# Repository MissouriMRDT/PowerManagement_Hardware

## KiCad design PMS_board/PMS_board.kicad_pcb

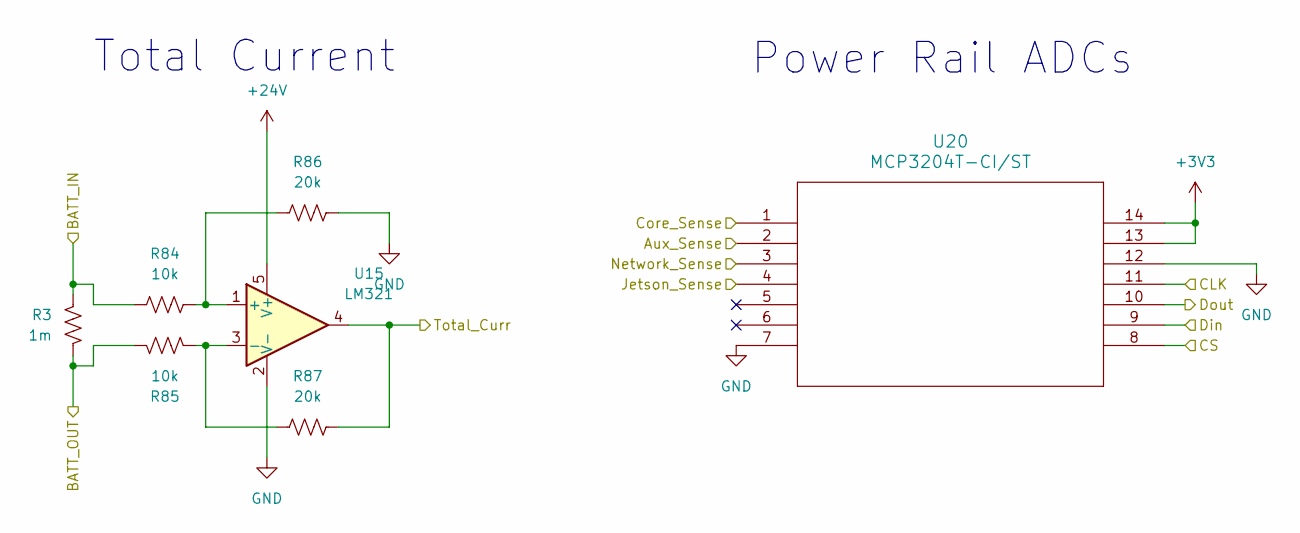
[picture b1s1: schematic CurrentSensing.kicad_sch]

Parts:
R3: 1m; ShuntSMD_BVT-M-R001-1.0
R84, R85: 10k; R_0603_1608Metric_Pad0.98x0.95mm_HandSolder
R86, R87: 20k; R_0603_1608Metric_Pad0.98x0.95mm_HandSolder
U15: LM321; SOT-23-5
U20: MCP3204T-CI/ST; TSSOP14_MC_MCH

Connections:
+3V3: U20.13, U20.14; also elsewhere on the board
+24V: U15.5 (V+); also elsewhere on the board
/Current Sensing/Aux_Sense: U20.2; also elsewhere on the board
/Current Sensing/BATT_OUT: R3.2, R85.1; also elsewhere on the board
/Current Sensing/CLK: U20.11; also elsewhere on the board
/Current Sensing/CS: U20.8; also elsewhere on the board
/Current Sensing/Core_Sense: U20.1; also elsewhere on the board
/Current Sensing/Din: U20.9; also elsewhere on the board
/Current Sensing/Dout: U20.10; also elsewhere on the board
/Current Sensing/Jetson_Sense: U20.4; also elsewhere on the board
/Current Sensing/Network_Sense: U20.3; also elsewhere on the board
/Current Sensing/Total_Curr: R87.2, U15.4; also elsewhere on the board
/HotSwap/Aalmout: R3.1, R84.1; also elsewhere on the board
GND: R86.2, U15.2 (V-), U20.7, U20.12; also elsewhere on the board
unnamed: R84.2, R86.1, U15.1 (+)
unnamed: R85.2, R87.1, U15.3 (-)

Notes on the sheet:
Total Current
Power Rail ADCs

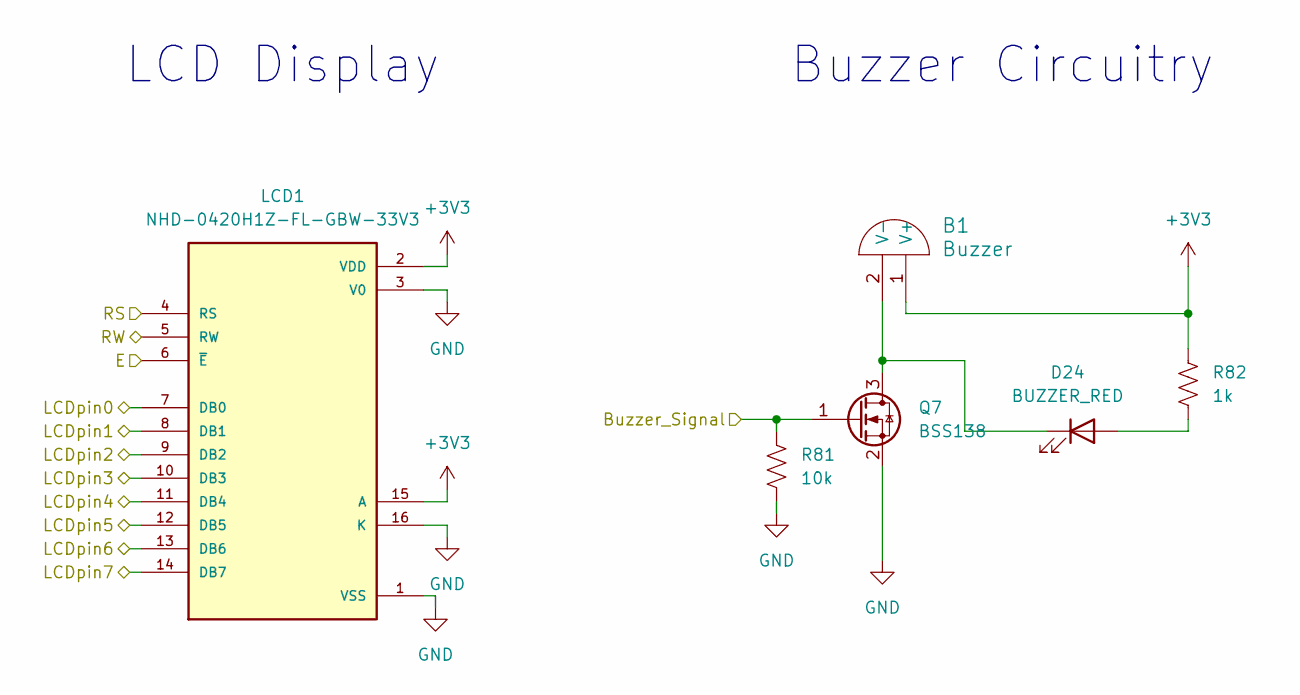
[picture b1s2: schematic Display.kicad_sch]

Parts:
B1: Buzzer; Buzzer_12x9.5RM7.6
D24: BUZZER_RED; LED_0603_1608Metric_Pad1.05x0.95mm_HandSolder
LCD1: NHD-0420H1Z-FL-GBW-33V3; LCD_NHD-0420H1Z-FL-GBW-33V3; PARTREV 02
Q7: BSS138; SOT-23
R81: 10k; R_0603_1608Metric_Pad0.98x0.95mm_HandSolder
R82: 1k; R_0603_1608Metric_Pad0.98x0.95mm_HandSolder

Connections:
+3V3: B1.1 (V+), LCD1.2 (VDD), LCD1.15 (A), R82.1; also elsewhere on the board
/Battery Display/Buzzer_Signal: Q7.1 (G), R81.1; also elsewhere on the board
/Battery Display/E: LCD1.6 (~E); also elsewhere on the board
/Battery Display/LCDpin0: LCD1.7 (DB0); also elsewhere on the board
/Battery Display/LCDpin1: LCD1.8 (DB1); also elsewhere on the board
/Battery Display/LCDpin2: LCD1.9 (DB2); also elsewhere on the board
/Battery Display/LCDpin3: LCD1.10 (DB3); also elsewhere on the board
/Battery Display/LCDpin4: LCD1.11 (DB4); also elsewhere on the board
/Battery Display/LCDpin5: LCD1.12 (DB5); also elsewhere on the board
/Battery Display/LCDpin6: LCD1.13 (DB6); also elsewhere on the board
/Battery Display/LCDpin7: LCD1.14 (DB7); also elsewhere on the board
/Battery Display/RS: LCD1.4 (RS); also elsewhere on the board
/Battery Display/RW: LCD1.5 (RW); also elsewhere on the board
GND: LCD1.1 (VSS), LCD1.3 (V0), LCD1.16 (K), Q7.2 (S), R81.2; also elsewhere on the board
unnamed: B1.2 (V-), D24.1 (K), Q7.3 (D)
unnamed: D24.2 (A), R82.2

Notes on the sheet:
Buzzer Circuitry
LCD Display

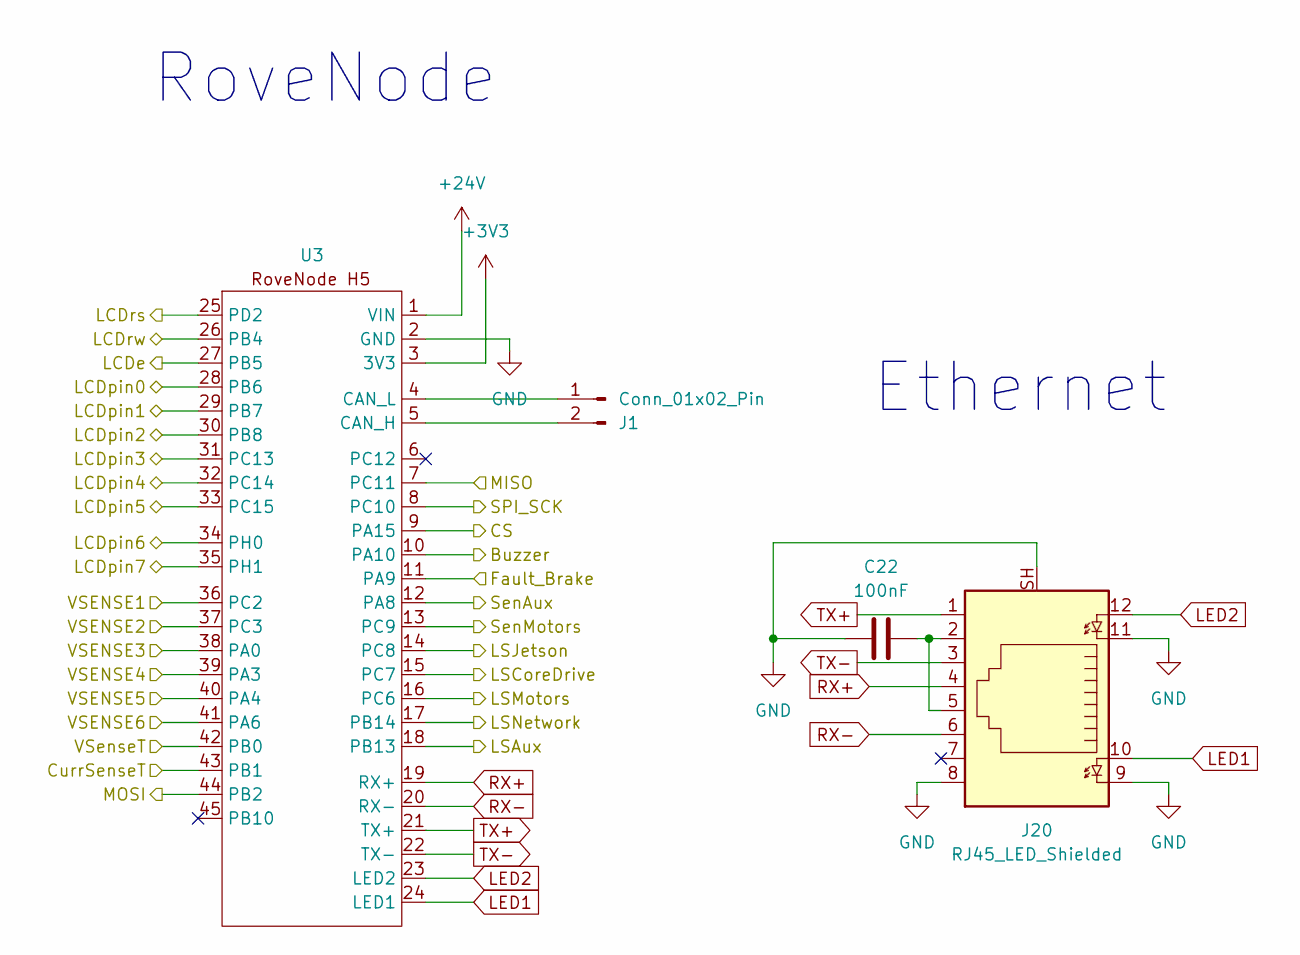
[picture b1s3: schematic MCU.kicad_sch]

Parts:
C22: 100nF; C_0603_1608Metric_Pad1.08x0.95mm_HandSolder
J1: Conn_01x02_Pin; JST_PH_B2B-PH-K_1x02_P2.00mm_Vertical
J20: RJ45_LED_Shielded; RJ45_Teensy
U3: RoveNode_H5

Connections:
+3V3: U3.3 (3V3); also elsewhere on the board
+24V: U3.1 (VIN); also elsewhere on the board
/Battery Display/Buzzer_Signal: U3.10 (PA10); also elsewhere on the board
/Battery Display/E: U3.27 (PB5); also elsewhere on the board
/Battery Display/LCDpin0: U3.28 (PB6); also elsewhere on the board
/Battery Display/LCDpin1: U3.29 (PB7); also elsewhere on the board
/Battery Display/LCDpin2: U3.30 (PB8); also elsewhere on the board
/Battery Display/LCDpin3: U3.31 (PC13); also elsewhere on the board
/Battery Display/LCDpin4: U3.32 (PC14); also elsewhere on the board
/Battery Display/LCDpin5: U3.33 (PC15); also elsewhere on the board
/Battery Display/LCDpin6: U3.34 (PH0); also elsewhere on the board
/Battery Display/LCDpin7: U3.35 (PH1); also elsewhere on the board
/Battery Display/RS: U3.25 (PD2); also elsewhere on the board
/Battery Display/RW: U3.26 (PB4); also elsewhere on the board
/Current Sensing/CLK: U3.8 (PC10); also elsewhere on the board
/Current Sensing/CS: U3.9 (PA15); also elsewhere on the board
/Current Sensing/Din: U3.44 (PB2); also elsewhere on the board
/Current Sensing/Dout: U3.7 (PC11); also elsewhere on the board
/Current Sensing/Total_Curr: U3.43 (PB1); also elsewhere on the board
/Load Switching + Outputs/Fault_Brakes: U3.11 (PA9); also elsewhere on the board
/Load Switching + Outputs/In_Aux: U3.18 (PB13); also elsewhere on the board
/Load Switching + Outputs/In_Boards: U3.15 (PC7); also elsewhere on the board
/Load Switching + Outputs/In_Jetson: U3.14 (PC8); also elsewhere on the board
/Load Switching + Outputs/In_Motors: U3.16 (PC6); also elsewhere on the board
/Load Switching + Outputs/In_Network: U3.17 (PB14); also elsewhere on the board
/Load Switching + Outputs/Sen_Aux: U3.12 (PA8); also elsewhere on the board
/Load Switching + Outputs/Sen_Motors: U3.13 (PC9); also elsewhere on the board
/Microcontroller/VSENSE1: U3.36 (PC2); also elsewhere on the board
/Microcontroller/VSENSE2: U3.37 (PC3); also elsewhere on the board
/Microcontroller/VSENSE3: U3.38 (PA0); also elsewhere on the board
/Microcontroller/VSENSE4: U3.39 (PA3); also elsewhere on the board
/Microcontroller/VSENSE5: U3.40 (PA4); also elsewhere on the board
/Microcontroller/VSENSE6: U3.41 (PA6); also elsewhere on the board
/Microcontroller/VSenseT: U3.42 (PB0); also elsewhere on the board
GND: C22.1, J20.8, J20.9, J20.11, J20.SH, U3.2 (GND); also elsewhere on the board
LED1: J20.10, U3.24 (LED1)
LED2: J20.12, U3.23 (LED2)
unnamed: C22.2, J20.2, J20.5
unnamed: J1.1, U3.4 (CAN_L)
unnamed: J1.2, U3.5 (CAN_H)
RX+: J20.4, U3.19 (RX+)
RX-: J20.6, U3.20 (RX-)
TX+: J20.1, U3.21 (TX+)
TX-: J20.3, U3.22 (TX-)

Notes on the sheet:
Ethernet
RoveNode

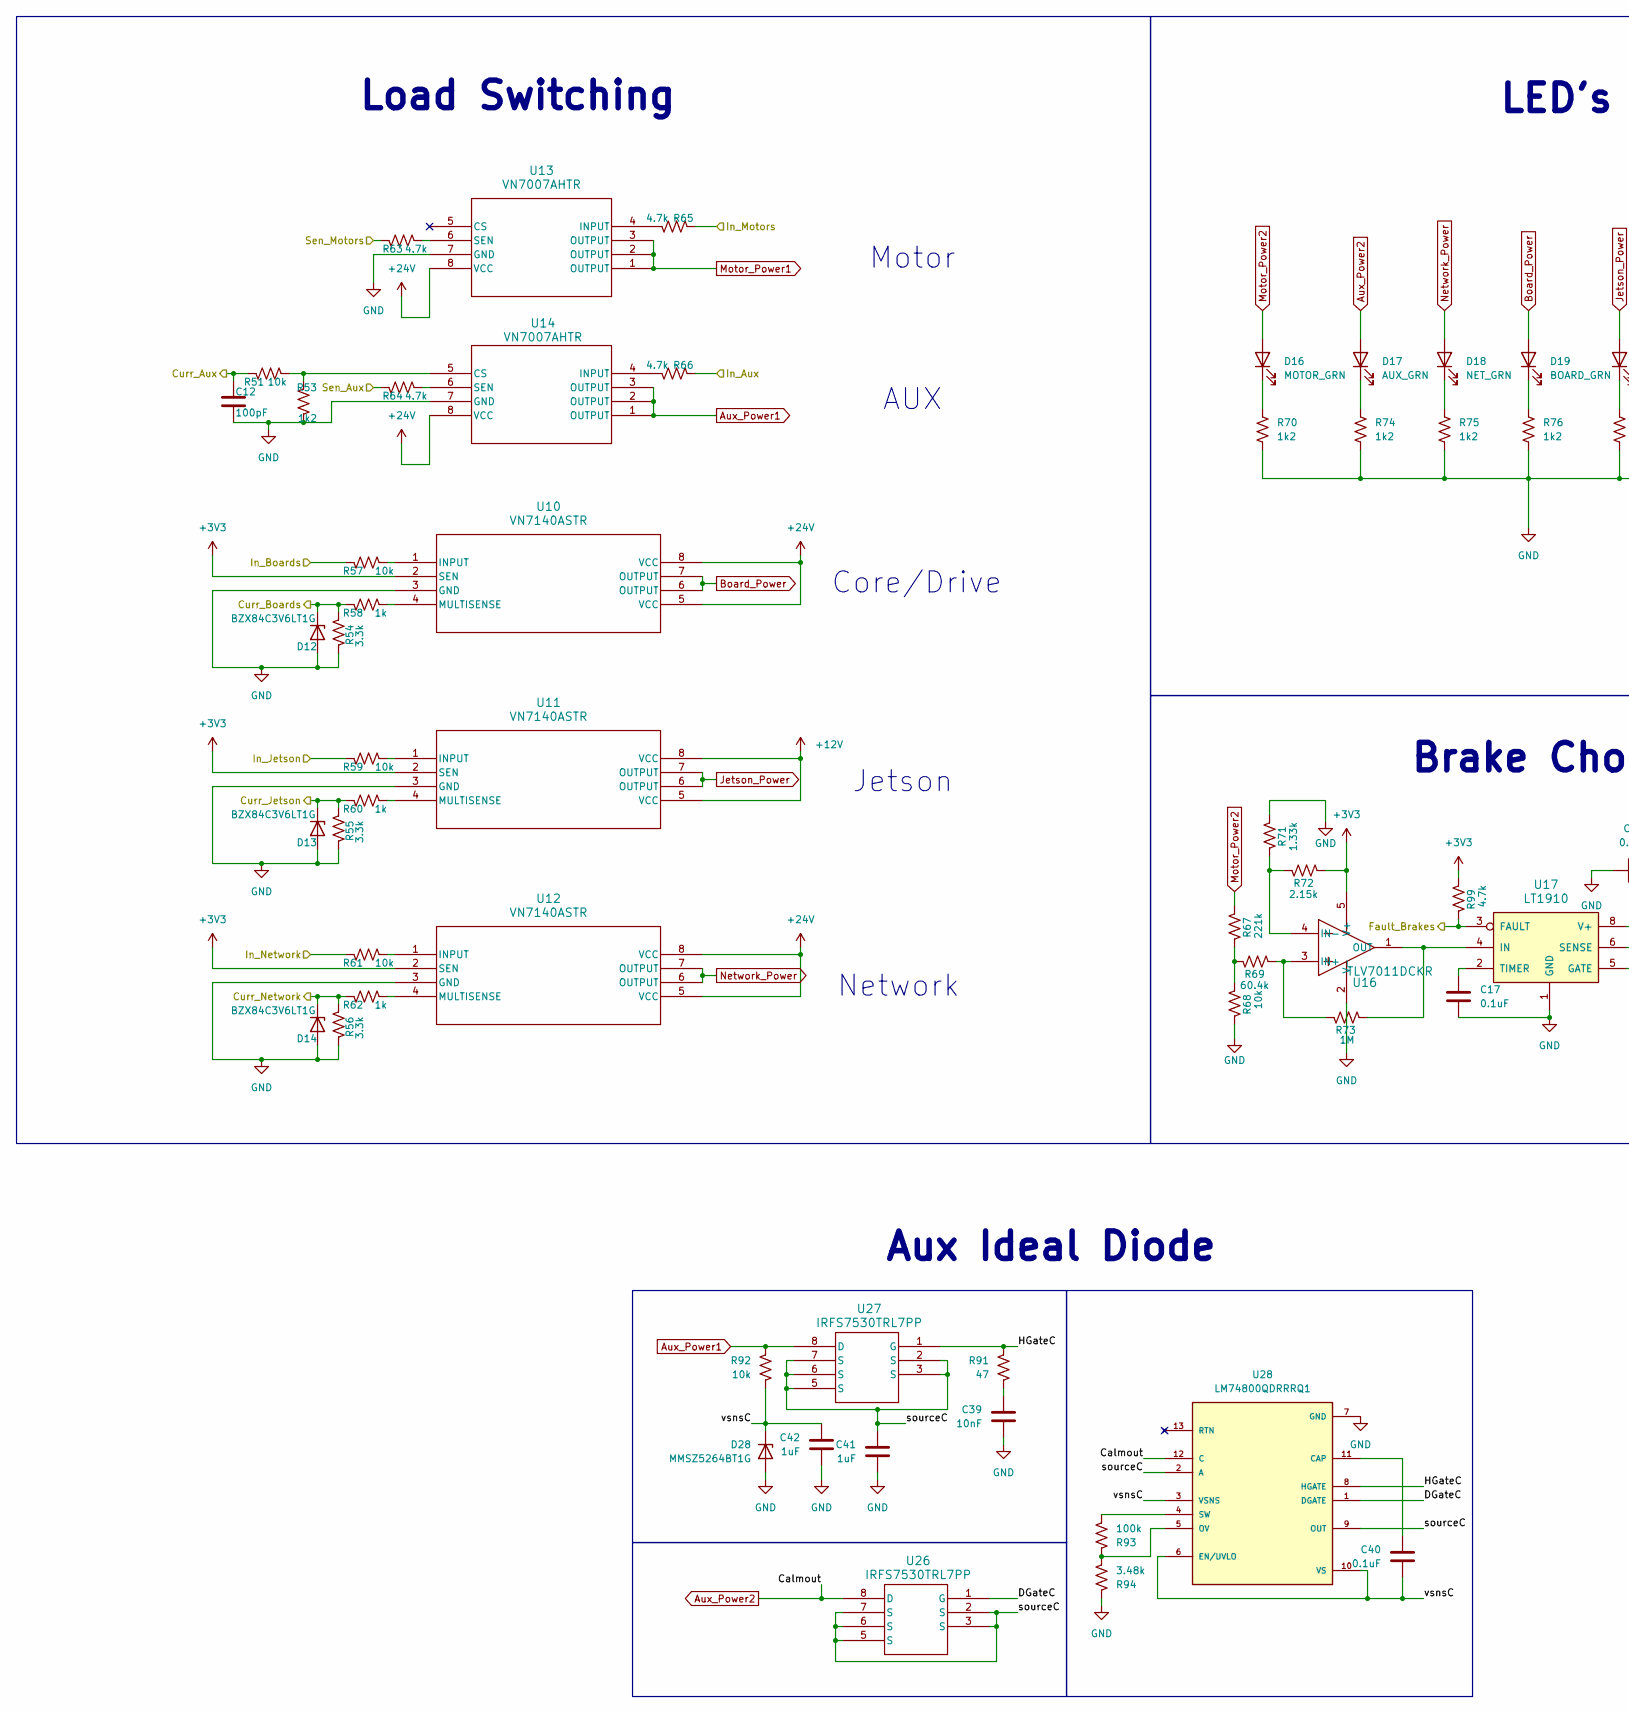
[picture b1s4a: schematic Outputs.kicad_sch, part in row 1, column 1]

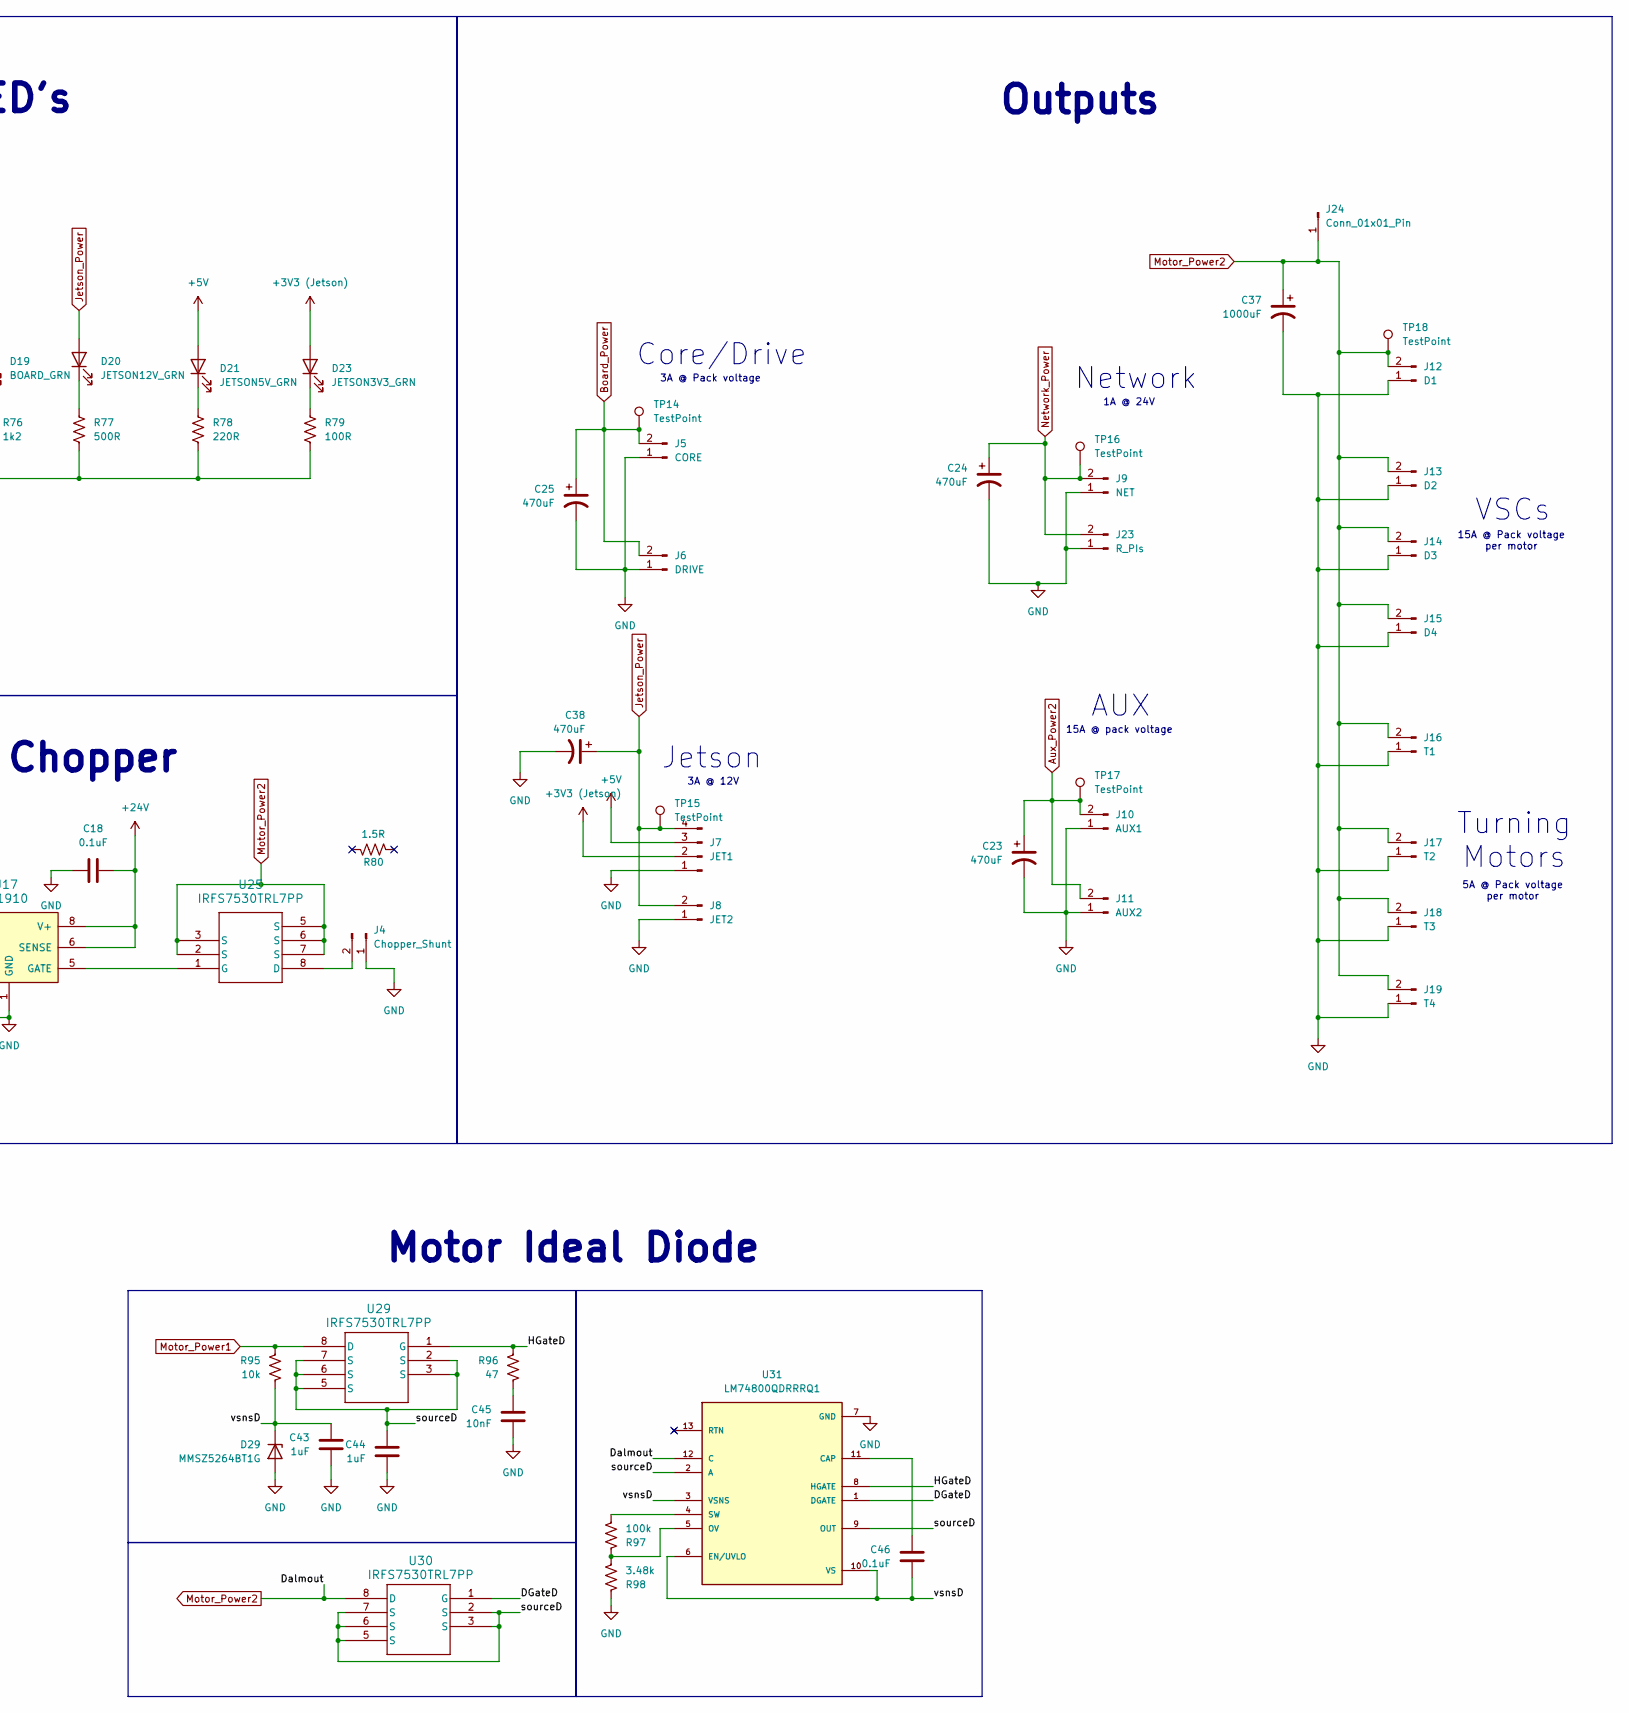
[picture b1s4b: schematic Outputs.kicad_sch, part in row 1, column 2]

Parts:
C12: 100pF; C_0603_1608Metric_Pad1.08x0.95mm_HandSolder
C17, C18, C40, C46: 0.1uF; C_0603_1608Metric_Pad1.08x0.95mm_HandSolder
C23, C24, C25, C38: 470uF; CP_Radial_D10.0mm_P5.00mm
C37: 1000uF; CP_Radial_D16.0mm_P7.50mm
C39, C45: 10nF; C_0603_1608Metric_Pad1.08x0.95mm_HandSolder
C41, C42, C43, C44: 1uF; C_0603_1608Metric_Pad1.08x0.95mm_HandSolder
D12, D13, D14: BZX84C3V6LT1G; SOT-23_Diode
D16: MOTOR_GRN; D_0603_1608Metric_Pad1.05x0.95mm_HandSolder
D17: AUX_GRN; D_0603_1608Metric_Pad1.05x0.95mm_HandSolder
D18: NET_GRN; D_0603_1608Metric_Pad1.05x0.95mm_HandSolder
D19: BOARD_GRN; D_0603_1608Metric_Pad1.05x0.95mm_HandSolder
D20: JETSON12V_GRN; D_0603_1608Metric_Pad1.05x0.95mm_HandSolder
D21: JETSON5V_GRN; D_0603_1608Metric_Pad1.05x0.95mm_HandSolder
D23: JETSON3V3_GRN; D_0603_1608Metric_Pad1.05x0.95mm_HandSolder
D28, D29: MMSZ5264BT1G; D_SOD-123
J4: Chopper_Shunt; MOLEX_MegaFit_02_Vertical
J5: CORE; MOLEX_MegaFit_02_Vertical
J6: DRIVE; MOLEX_MegaFit_02_Vertical
J7: JET1; MOLEX_SL_04_Vertical
J8: JET2; MOLEX_MegaFit_02_Vertical
J9: NET; MOLEX_MegaFit_02_Vertical
J10: AUX1; MOLEX_MegaFit_02_Vertical
J11: AUX2; MOLEX_MegaFit_02_Vertical
J12: D1; MOLEX_MegaFit_02_Vertical
J13: D2; MOLEX_MegaFit_02_Vertical
J14: D3; MOLEX_MegaFit_02_Vertical
J15: D4; MOLEX_MegaFit_02_Vertical
J16: T1; MOLEX_MegaFit_02_Vertical
J17: T2; MOLEX_MegaFit_02_Vertical
J18: T3; MOLEX_MegaFit_02_Vertical
J19: T4; MOLEX_MegaFit_02_Vertical
J23: R_PIs; MOLEX_MegaFit_02_Vertical
J24: Conn_01x01_Pin; Square_Anderson_1_V
R51, R57, R59, R61, R68, R92, R95: 10k; R_0603_1608Metric_Pad0.98x0.95mm_HandSolder
R53, R70, R74, R75, R76: 1k2; R_0603_1608Metric_Pad0.98x0.95mm_HandSolder
R54, R55, R56: 3.3k; R_0603_1608Metric_Pad0.98x0.95mm_HandSolder
R58, R60, R62: 1k; R_0603_1608Metric_Pad0.98x0.95mm_HandSolder
R63, R64, R65, R66, R99: 4.7k; R_0603_1608Metric_Pad0.98x0.95mm_HandSolder
R67: 221k; R_0603_1608Metric_Pad0.98x0.95mm_HandSolder
R69: 60.4k; R_0603_1608Metric_Pad0.98x0.95mm_HandSolder
R71: 1.33k; R_0603_1608Metric_Pad0.98x0.95mm_HandSolder
R72: 2.15k; R_0603_1608Metric_Pad0.98x0.95mm_HandSolder
R73: 1M; R_0603_1608Metric_Pad0.98x0.95mm_HandSolder
R77: 500R; R_0603_1608Metric_Pad0.98x0.95mm_HandSolder
R78: 220R; R_0603_1608Metric_Pad0.98x0.95mm_HandSolder
R79: 100R; R_0603_1608Metric_Pad0.98x0.95mm_HandSolder
R80: 1.5R
R91, R96: 47; R_0603_1608Metric_Pad0.98x0.95mm_HandSolder
R93, R97: 100k; R_0603_1608Metric_Pad0.98x0.95mm_HandSolder
R94, R98: 3.48k; R_0603_1608Metric_Pad0.98x0.95mm_HandSolder
TP14, TP15, TP16, TP17, TP18: TestPoint; TestPoint_Pad_D1.0mm
U10, U11, U12: VN7140ASTR; SO-8_STM
U13, U14: VN7007AHTR; OCTOPAK_STM
U16: TLV7011DCKR; DCK0005A_N
U17: LT1910; SO-8_3.9x4.9mm_P1.27mm
U25, U26, U27, U29, U30: IRFS7530TRL7PP; PG-TO263-7_INF
U28, U31: LM74800QDRRRQ1; IC_LM74800QDRRRQ1; PARTREV C

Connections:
+3V3: R72.2, R99.2, U10.2 (SEN), U11.2 (SEN), U12.2 (SEN), U16.5 (V+); also elsewhere on the board
+3V3 (Jetson): D23.2 (A), J7.2; also elsewhere on the board
+5V: D21.2 (A), J7.3; also elsewhere on the board
+12V: U11.5 (VCC), U11.8 (VCC); also elsewhere on the board
+24V: C18.2, U10.5 (VCC), U10.8 (VCC), U12.5 (VCC), U12.8 (VCC), U13.8 (VCC), U14.8 (VCC), U17.6 (SENSE), U17.8 (V+); also elsewhere on the board
/Current Sensing/Aux_Sense: C12.2, R51.2; also elsewhere on the board
/Current Sensing/Core_Sense: D12.1 (K), R54.2, R58.1; also elsewhere on the board
/Current Sensing/Jetson_Sense: D13.1 (K), R55.2, R60.1; also elsewhere on the board
/Current Sensing/Network_Sense: D14.1 (K), R56.2, R62.1; also elsewhere on the board
/Load Switching + Outputs/DGateC: U26.1 (G), U28.1 (DGATE)
/Load Switching + Outputs/DGateD: U30.1 (G), U31.1 (DGATE)
/Load Switching + Outputs/Fault_Brakes: R99.1, U17.3 (FAULT); also elsewhere on the board
/Load Switching + Outputs/HGateC: R91.1, U27.1 (G), U28.8 (HGATE)
/Load Switching + Outputs/HGateD: R96.1, U29.1 (G), U31.8 (HGATE)
/Load Switching + Outputs/In_Aux: R66.2; also elsewhere on the board
/Load Switching + Outputs/In_Boards: R57.1; also elsewhere on the board
/Load Switching + Outputs/In_Jetson: R59.1; also elsewhere on the board
/Load Switching + Outputs/In_Motors: R65.2; also elsewhere on the board
/Load Switching + Outputs/In_Network: R61.1; also elsewhere on the board
/Load Switching + Outputs/Sen_Aux: R64.2; also elsewhere on the board
/Load Switching + Outputs/Sen_Motors: R63.2; also elsewhere on the board
/Load Switching + Outputs/sourceC: C41.1, U26.2 (S), U26.3 (S), U26.5 (S), U26.6 (S), U26.7 (S), U27.2 (S), U27.3 (S), U27.5 (S), U27.6 (S), U27.7 (S), U28.2 (A), U28.9 (OUT)
/Load Switching + Outputs/sourceD: C44.1, U29.2 (S), U29.3 (S), U29.5 (S), U29.6 (S), U29.7 (S), U30.2 (S), U30.3 (S), U30.5 (S), U30.6 (S), U30.7 (S), U31.2 (A), U31.9 (OUT)
/Load Switching + Outputs/vsnsC: C40.2, C42.1, D28.1 (K), R92.1, U28.3 (VSNS), U28.6 (EN/UVLO), U28.10 (VS)
/Load Switching + Outputs/vsnsD: C43.1, C46.2, D29.1 (K), R95.1, U31.3 (VSNS), U31.6 (EN/UVLO), U31.10 (VS)
Aux_Power1: R92.2, U14.1 (OUTPUT), U14.2 (OUTPUT), U14.3 (OUTPUT), U27.8 (D)
Aux_Power2: C23.1, D17.2 (A), J10.2, J11.2, TP17.1 (1_1), U26.8 (D), U28.12 (C)
Board_Power: C25.1, D19.2 (A), J5.2, J6.2, TP14.1 (1_1), U10.6 (OUTPUT), U10.7 (OUTPUT)
GND: C12.1, C17.2, C18.1, C23.2, C24.2, C25.2, C37.2, C38.2, C39.2, C41.2, C42.2, C43.2, C44.2, C45.2, D12.2 (A), D13.2 (A), D14.2 (A), D28.2 (A), D29.2 (A), J4.1, J5.1, J6.1, J7.1, J8.1, J9.1, J10.1, J11.1, J12.1, J13.1, J14.1, J15.1, J16.1, J17.1, J18.1, J19.1, J23.1, R53.2, R54.1, R55.1, R56.1, R68.1, R70.2, R71.2, R74.2, R75.2, R76.2, R77.2, R78.2, R79.2, R94.1, R98.1, U10.3 (GND), U11.3 (GND), U12.3 (GND), U13.7 (GND), U14.7 (GND), U16.2 (V-), U17.1 (GND), U28.7 (GND), U31.7 (GND); also elsewhere on the board
Jetson_Power: C38.1, D20.2 (A), J7.4, J8.2, TP15.1 (1_1), U11.6 (OUTPUT), U11.7 (OUTPUT)
Motor_Power1: R95.2, U13.1 (OUTPUT), U13.2 (OUTPUT), U13.3 (OUTPUT), U29.8 (D)
Motor_Power2: C37.1, D16.2 (A), J12.2, J13.2, J14.2, J15.2, J16.2, J17.2, J18.2, J19.2, J24.1 (Pin_1_1), R67.2, TP18.1 (1_1), U25.2 (S), U25.3 (S), U25.5 (S), U25.6 (S), U25.7 (S), U30.8 (D), U31.12 (C)
unnamed: C39.1, R91.2
unnamed: C45.1, R96.2
unnamed: D16.1 (K), R70.1
unnamed: D17.1 (K), R74.1
unnamed: D18.1 (K), R75.1
unnamed: D19.1 (K), R76.1
unnamed: D20.1 (K), R77.1
unnamed: D21.1 (K), R78.1
unnamed: D23.1 (K), R79.1
unnamed: J4.2, U25.8 (D)
unnamed: R67.1, R68.2, R69.1
unnamed: R57.2, U10.1 (INPUT)
unnamed: R58.2, U10.4 (MULTISENSE)
unnamed: R59.2, U11.1 (INPUT)
unnamed: R60.2, U11.4 (MULTISENSE)
unnamed: R61.2, U12.1 (INPUT)
unnamed: R62.2, U12.4 (MULTISENSE)
unnamed: R65.1, U13.4 (INPUT)
unnamed: R63.1, U13.6 (SEN)
unnamed: R51.1, R53.1, U14.5 (CS)
unnamed: R66.1, U14.4 (INPUT)
unnamed: R64.1, U14.6 (SEN)
unnamed: R69.2, R73.1, U16.3 (IN+)
unnamed: R71.1, R72.1, U16.4 (IN-)
unnamed: R73.2, U16.1 (OUT), U17.4 (IN)
unnamed: U17.5 (GATE), U25.1 (G)
unnamed: C17.1, U17.2 (TIMER)
unnamed: C40.1, U28.11 (CAP)
unnamed: R93.1, R94.2, U28.5 (OV)
unnamed: R93.2, U28.4 (SW)
unnamed: C46.1, U31.11 (CAP)
unnamed: R97.1, R98.2, U31.5 (OV)
unnamed: R97.2, U31.4 (SW)
Network_Power: C24.1, D18.2 (A), J9.2, J23.2, TP16.1 (1_1), U12.6 (OUTPUT), U12.7 (OUTPUT)

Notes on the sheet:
Aux Ideal Diode
Jetson
Outputs
15A @ Pack voltage per motor
Motor
AUX
Motor Ideal Diode
Core/Drive
Turning Motors
3A @ 12V
3A @ Pack voltage
Network
1A @ 24V
VSCs
LED's
Brake Chopper
Core/Drive
Load Switching
Jetson
5A @ Pack voltage per motor
15A @ pack voltage

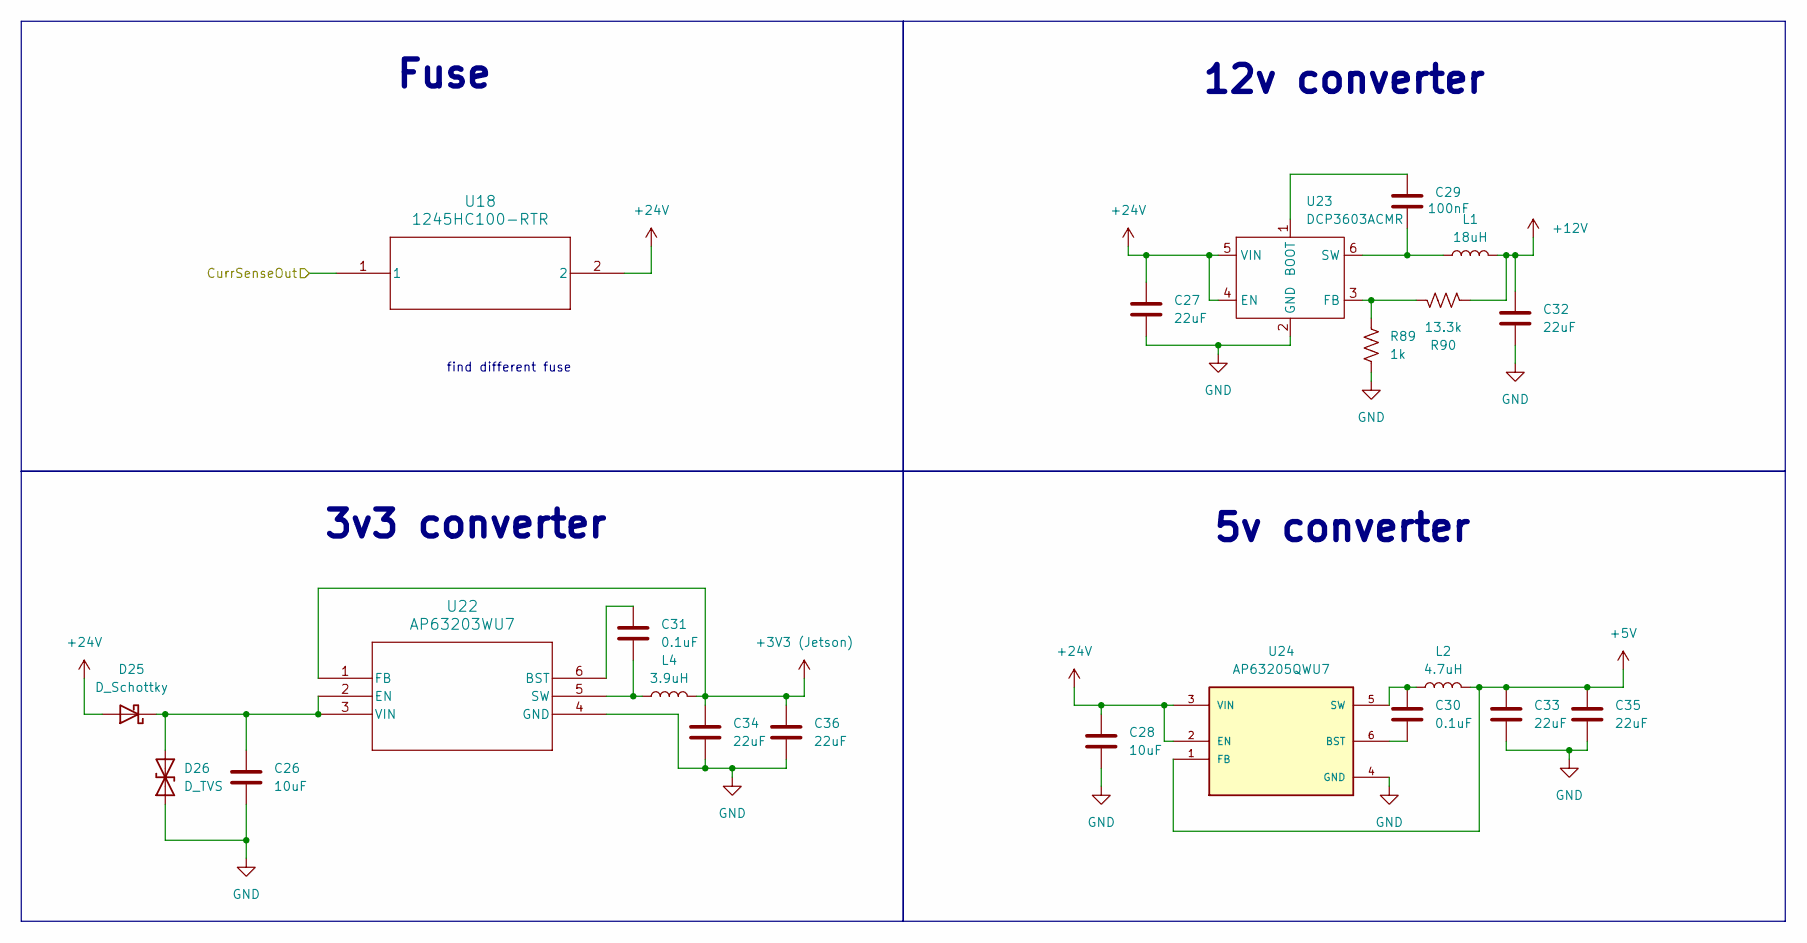
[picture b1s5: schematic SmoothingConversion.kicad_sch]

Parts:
C26, C28: 10uF; C_0603_1608Metric_Pad1.08x0.95mm_HandSolder
C27, C32, C33, C34, C35, C36: 22uF; C_1210_3225Metric_Pad1.33x2.70mm_HandSolder
C29: 100nF; C_0603_1608Metric_Pad1.08x0.95mm_HandSolder
C30, C31: 0.1uF; C_0603_1608Metric_Pad1.08x0.95mm_HandSolder
D25: D_Schottky; D_SOD-123F
D26: D_TVS; D_Wurth_WE-TVSP-DO214-AC-400W_BI
L1: 18uH; IND_BOURNS_SRR1210
L2: 4.7uH; L_Bourns_SRR1210A
L4: 3.9uH; L_1812_4532Metric_Pad1.30x3.40mm_HandSolder
R89: 1k; R_0603_1608Metric_Pad0.98x0.95mm_HandSolder
R90: 13.3k; R_0603_1608Metric_Pad0.98x0.95mm_HandSolder
U18: 1245HC100-RTR; 1245HC100-RTR_COB
U22: AP63203WU7; SO8_DCK_TEX
U23: DCP3603ACMR; TSOT-23-6_HandSoldering
U24: AP63205QWU7; SOT95P280X100-6N; PARTREV 1 - 2; DigiKey_Part_Number 31-AP63205QWU-7CT-ND

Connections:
+3V3 (Jetson): C34.1, C36.1, L4.2, U22.1 (FB); also elsewhere on the board
+5V: C33.1, C35.1, L2.2, U24.1 (FB); also elsewhere on the board
+12V: C32.1, L1.2, R90.2; also elsewhere on the board
+24V: C27.1, C28.1, D25.2 (A), U18.2, U23.4 (EN), U23.5 (VIN), U24.2 (EN), U24.3 (VIN); also elsewhere on the board
/Current Sensing/BATT_OUT: U18.1; also elsewhere on the board
GND: C26.2, C27.2, C28.2, C32.2, C33.2, C34.2, C35.2, C36.2, D26.1 (A1), R89.2, U22.4 (GND), U23.2 (GND), U24.4 (GND); also elsewhere on the board
unnamed: C26.1, D25.1 (K), D26.2 (A2), U22.2 (EN), U22.3 (VIN)
unnamed: C31.1, U22.6 (BST)
unnamed: C31.2, L4.1, U22.5 (SW)
unnamed: C29.1, U23.1 (BOOT)
unnamed: R89.1, R90.1, U23.3 (FB)
unnamed: C29.2, L1.1, U23.6 (SW)
unnamed: C30.2, U24.6 (BST)
unnamed: C30.1, L2.1, U24.5 (SW)

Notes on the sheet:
Fuse
5v converter
3v3 converter
12v converter
find different fuse
